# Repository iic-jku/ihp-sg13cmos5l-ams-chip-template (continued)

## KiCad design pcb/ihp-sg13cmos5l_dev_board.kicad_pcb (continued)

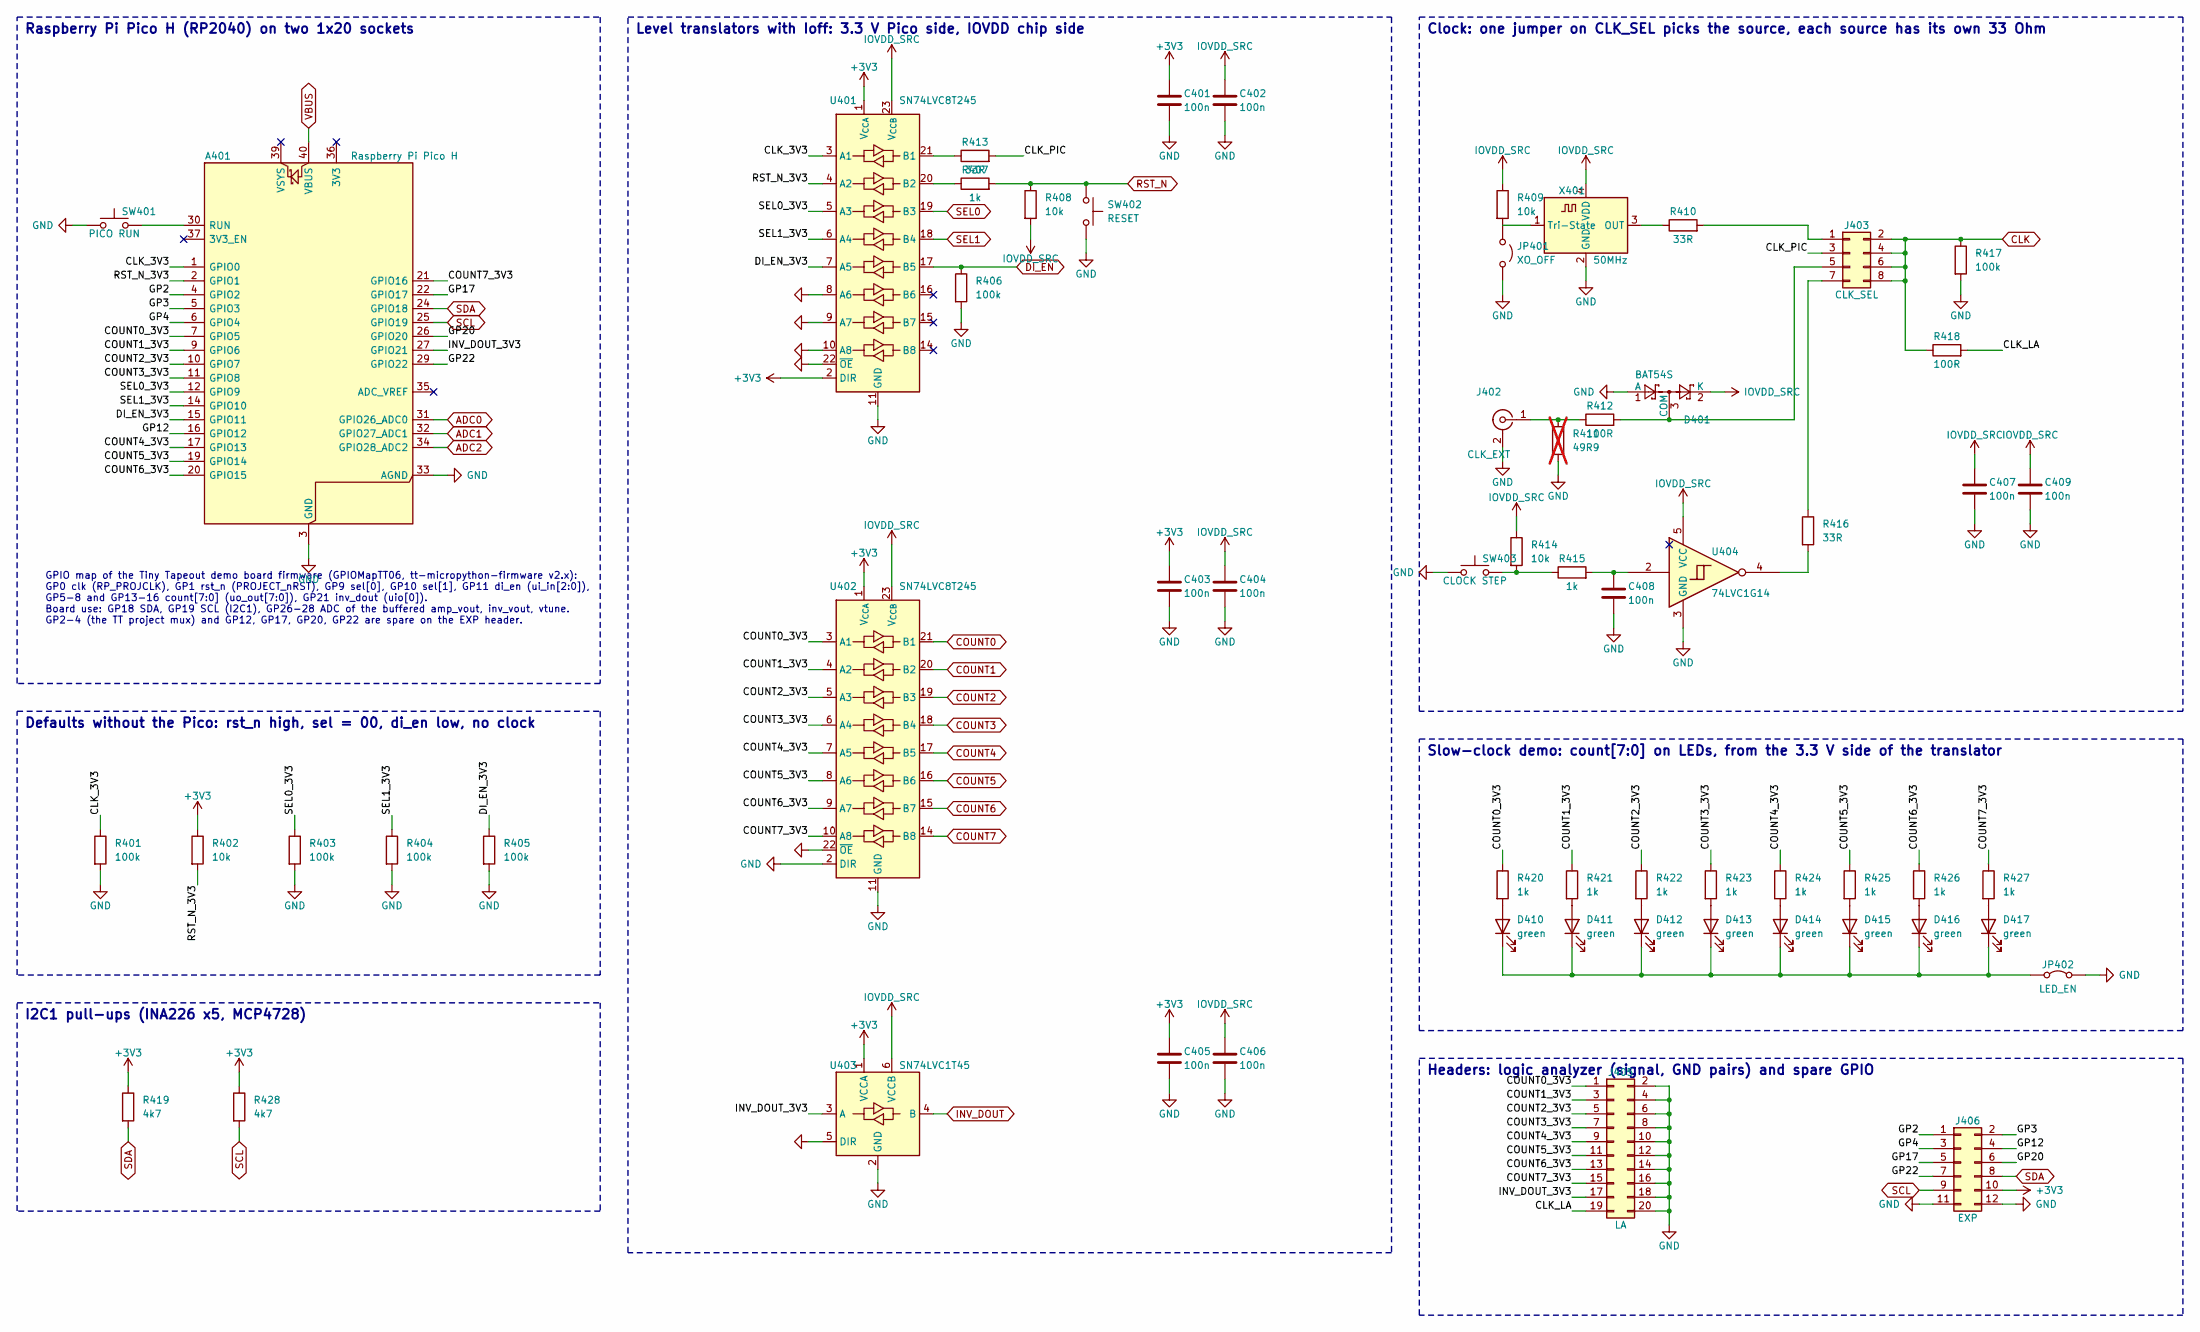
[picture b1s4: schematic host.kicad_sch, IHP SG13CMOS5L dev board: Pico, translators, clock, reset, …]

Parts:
A401: Raspberry Pi Pico H; RaspberryPi_Pico_H_Sockets; MPN SC0917
C401, C402, C403, C404, C405, C406, C407, C408, C409: 100n; C_0603_1608Metric_Pad1.08x0.95mm_HandSolder; MPN CL10B104KB8NNNC
D401: BAT54S; SOT-23; MPN BAT54SLT1G
D410, D411, D412, D413, D414, D415, D416, D417: green; LED_0603_1608Metric_Pad1.05x0.95mm_HandSolder; MPN APT1608LZGCK
J402: CLK_EXT; BNC_Amphenol_B6252HB-NPP3G-50_Horizontal_BoardEdge; MPN B6252HB-NPP3G-50
J403: CLK_SEL; PinHeader_2x04_P2.54mm_Vertical
J405: LA; PinHeader_2x10_P2.54mm_Vertical
J406: EXP; PinHeader_2x06_P2.54mm_Vertical
JP401: XO_OFF; PinHeader_1x02_P2.54mm_Vertical
JP402: LED_EN; PinHeader_1x02_P2.54mm_Vertical
R401, R403, R404, R405, R406, R417: 100k; R_0603_1608Metric_Pad0.98x0.95mm_HandSolder; MPN RC0603FR-07100KL
R402, R408, R409, R414: 10k; R_0603_1608Metric_Pad0.98x0.95mm_HandSolder; MPN RC0603FR-0710KL
R407, R415, R420, R421, R422, R423, R424, R425, R426, R427: 1k; R_0603_1608Metric_Pad0.98x0.95mm_HandSolder; MPN RC0603FR-071KL
R410, R413, R416: 33R; R_0603_1608Metric_Pad0.98x0.95mm_HandSolder; MPN RC0603FR-0733RL
R411: 49R9; R_1206_3216Metric_Pad1.30x1.75mm_HandSolder; MPN RC1206FR-0749R9L; not fitted
R412, R418: 100R; R_0603_1608Metric_Pad0.98x0.95mm_HandSolder; MPN RC0603FR-07100RL
R419, R428: 4k7; R_0603_1608Metric_Pad0.98x0.95mm_HandSolder; MPN RC0603FR-074K7L
SW401: PICO RUN; SW_TH_Tactile_Omron_B3F-100x; MPN B3F-1000
SW402: RESET; SW_TH_Tactile_Omron_B3F-100x; MPN B3F-1000
SW403: CLOCK STEP; SW_TH_Tactile_Omron_B3F-100x; MPN B3F-1000
U401, U402: SN74LVC8T245; TSSOP-24_4.4x7.8mm_P0.65mm; MPN SN74LVC8T245PWR
U403: SN74LVC1T45; SOT-23-6; MPN SN74LVC1T45DBVR
U404: 74LVC1G14; SOT-23-5; MPN SN74LVC1G14DBVR
X401: 50MHz; Oscillator_SMD_Abracon_ASE-4Pin_3.2x2.5mm_HandSoldering; MPN ECS-3225MV-500-BN-TR

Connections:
+3V3: C401.1, C403.1, C405.1, J406.10, R402.1, R419.1, R428.1, U401.1 (V_{CCA}), U401.2 (DIR), U402.1 (V_{CCA}), U403.1 (VCCA); also elsewhere on the board
/Host/CLK_3V3: A401.1 (GPIO0), R401.1, U401.3 (A1)
/Host/CLK_LA: J405.19, R418.2
/Host/CLK_PIC: J403.3, R413.2
/Host/COUNT0_3V3: A401.7 (GPIO5), J405.1, R420.1, U402.3 (A1)
/Host/COUNT1_3V3: A401.9 (GPIO6), J405.3, R421.1, U402.4 (A2)
/Host/COUNT2_3V3: A401.10 (GPIO7), J405.5, R422.1, U402.5 (A3)
/Host/COUNT3_3V3: A401.11 (GPIO8), J405.7, R423.1, U402.6 (A4)
/Host/COUNT4_3V3: A401.17 (GPIO13), J405.9, R424.1, U402.7 (A5)
/Host/COUNT5_3V3: A401.19 (GPIO14), J405.11, R425.1, U402.8 (A6)
/Host/COUNT6_3V3: A401.20 (GPIO15), J405.13, R426.1, U402.9 (A7)
/Host/COUNT7_3V3: A401.21 (GPIO16), J405.15, R427.1, U402.10 (A8)
/Host/DI_EN_3V3: A401.15 (GPIO11), R405.1, U401.7 (A5)
/Host/GP2: A401.4 (GPIO2), J406.1
/Host/GP3: A401.5 (GPIO3), J406.2
/Host/GP4: A401.6 (GPIO4), J406.3
/Host/GP12: A401.16 (GPIO12), J406.4
/Host/GP17: A401.22 (GPIO17), J406.5
/Host/GP20: A401.26 (GPIO20), J406.6
/Host/GP22: A401.29 (GPIO22), J406.7
/Host/INV_DOUT_3V3: A401.27 (GPIO21), J405.17, U403.3 (A)
/Host/RST_N_3V3: A401.2 (GPIO1), R402.2, U401.4 (A2)
/Host/SEL0_3V3: A401.12 (GPIO9), R403.1, U401.5 (A3)
/Host/SEL1_3V3: A401.14 (GPIO10), R404.1, U401.6 (A4)
ADC0: A401.31 (GPIO26_ADC0); also elsewhere on the board
ADC1: A401.32 (GPIO27_ADC1); also elsewhere on the board
ADC2: A401.34 (GPIO28_ADC2); also elsewhere on the board
CLK: J403.2, J403.4, J403.6, J403.8, R417.1, R418.1; also elsewhere on the board
COUNT0: U402.21 (B1); also elsewhere on the board
COUNT1: U402.20 (B2); also elsewhere on the board
COUNT2: U402.19 (B3); also elsewhere on the board
COUNT3: U402.18 (B4); also elsewhere on the board
COUNT4: U402.17 (B5); also elsewhere on the board
COUNT5: U402.16 (B6); also elsewhere on the board
COUNT6: U402.15 (B7); also elsewhere on the board
COUNT7: U402.14 (B8); also elsewhere on the board
DI_EN: R406.1, U401.17 (B5); also elsewhere on the board
GND: A401.3 (GND), A401.8 (GND), A401.13 (GND), A401.18 (GND), A401.23 (GND), A401.28 (GND), A401.33 (AGND), A401.38 (GND), C401.2, C402.2, C403.2, C404.2, C405.2, C406.2, C407.2, C408.2, C409.2, D401.1 (A), J402.2 (Ext), J405.2, J405.4, J405.6, J405.8, J405.10, J405.12, J405.14, J405.16, J405.18, J405.20, J406.11, J406.12, JP401.2 (B), JP402.2 (B), R401.2, R403.2, R404.2, R405.2, R406.2, R411.2, R417.2, SW401.1, SW402.2, SW403.1, U401.8 (A6), U401.9 (A7), U401.10 (A8), U401.11 (GND), U401.12 (GND), U401.13 (GND), U401.22 (~OE), U402.2 (DIR), U402.11 (GND), U402.12 (GND), U402.13 (GND), U402.22 (~OE), U403.2 (GND), U403.5 (DIR), U404.3 (GND), X401.2 (GND); also elsewhere on the board
INV_DOUT: U403.4 (B); also elsewhere on the board
IOVDD_SRC: C402.1, C404.1, C406.1, C407.1, C409.1, D401.2 (K), R408.2, R409.1, R414.1, U401.23 (V_{CCB}), U401.24 (V_{CCB}), U402.23 (V_{CCB}), U402.24 (V_{CCB}), U403.6 (VCCB), U404.5 (VCC), X401.4 (VDD); also elsewhere on the board
unnamed: A401.30 (RUN), SW401.2
unnamed: C408.1, R415.2, U404.2
unnamed: D401.3 (COM), J403.5, R412.2
unnamed: D410.2 (A), R420.2
unnamed: D410.1 (K), D411.1 (K), D412.1 (K), D413.1 (K), D414.1 (K), D415.1 (K), D416.1 (K), D417.1 (K), JP402.1 (A)
unnamed: D411.2 (A), R421.2
unnamed: D412.2 (A), R422.2
unnamed: D413.2 (A), R423.2
unnamed: D414.2 (A), R424.2
unnamed: D415.2 (A), R425.2
unnamed: D416.2 (A), R426.2
unnamed: D417.2 (A), R427.2
unnamed: J402.1 (In), R411.1, R412.1
unnamed: J403.1, R410.2
unnamed: J403.7, R416.1
unnamed: JP401.1 (A), R409.2, X401.1 (Tri-State)
unnamed: R414.2, R415.1, SW403.2
unnamed: R416.2, U404.4
unnamed: R413.1, U401.21 (B1)
unnamed: R407.1, U401.20 (B2)
unnamed: R410.1, X401.3 (OUT)
RST_N: R407.2, R408.1, SW402.1; also elsewhere on the board
SCL: A401.25 (GPIO19), J406.9, R428.2; also elsewhere on the board
SDA: A401.24 (GPIO18), J406.8, R419.2; also elsewhere on the board
SEL0: U401.19 (B3); also elsewhere on the board
SEL1: U401.18 (B4); also elsewhere on the board
VBUS: A401.40 (VBUS); also elsewhere on the board

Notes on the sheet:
Raspberry Pi Pico H (RP2040) on two 1x20 sockets
GPIO map of the Tiny Tapeout demo board firmware (GPIOMapTT06, tt-micropython-firmware v2.x): GP0 clk (RP_PROJCLK), GP1 rst_n (PROJECT_nRST), GP9 sel[0], GP10 sel[1], GP11 di_en (ui_in[2:0]), GP5-8 and GP13-16 count[7:0] (uo_out[7:0]), GP21 inv_dout (uio[0]). Board use: GP18 SDA, GP19 SCL (I2C1), G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
Defaults without the Pico: rst_n high, sel = 00, di_en low, no clock
I2C1 pull-ups (INA226 x5, MCP4728)
Level translators with Ioff: 3.3 V Pico side, IOVDD chip side
Clock: one jumper on CLK_SEL picks the source, each source has its own 33 Ohm
Slow-clock demo: count[7:0] on LEDs, from the 3.3 V side of the translator
Headers: logic analyzer (signal, GND pairs) and spare GPIO

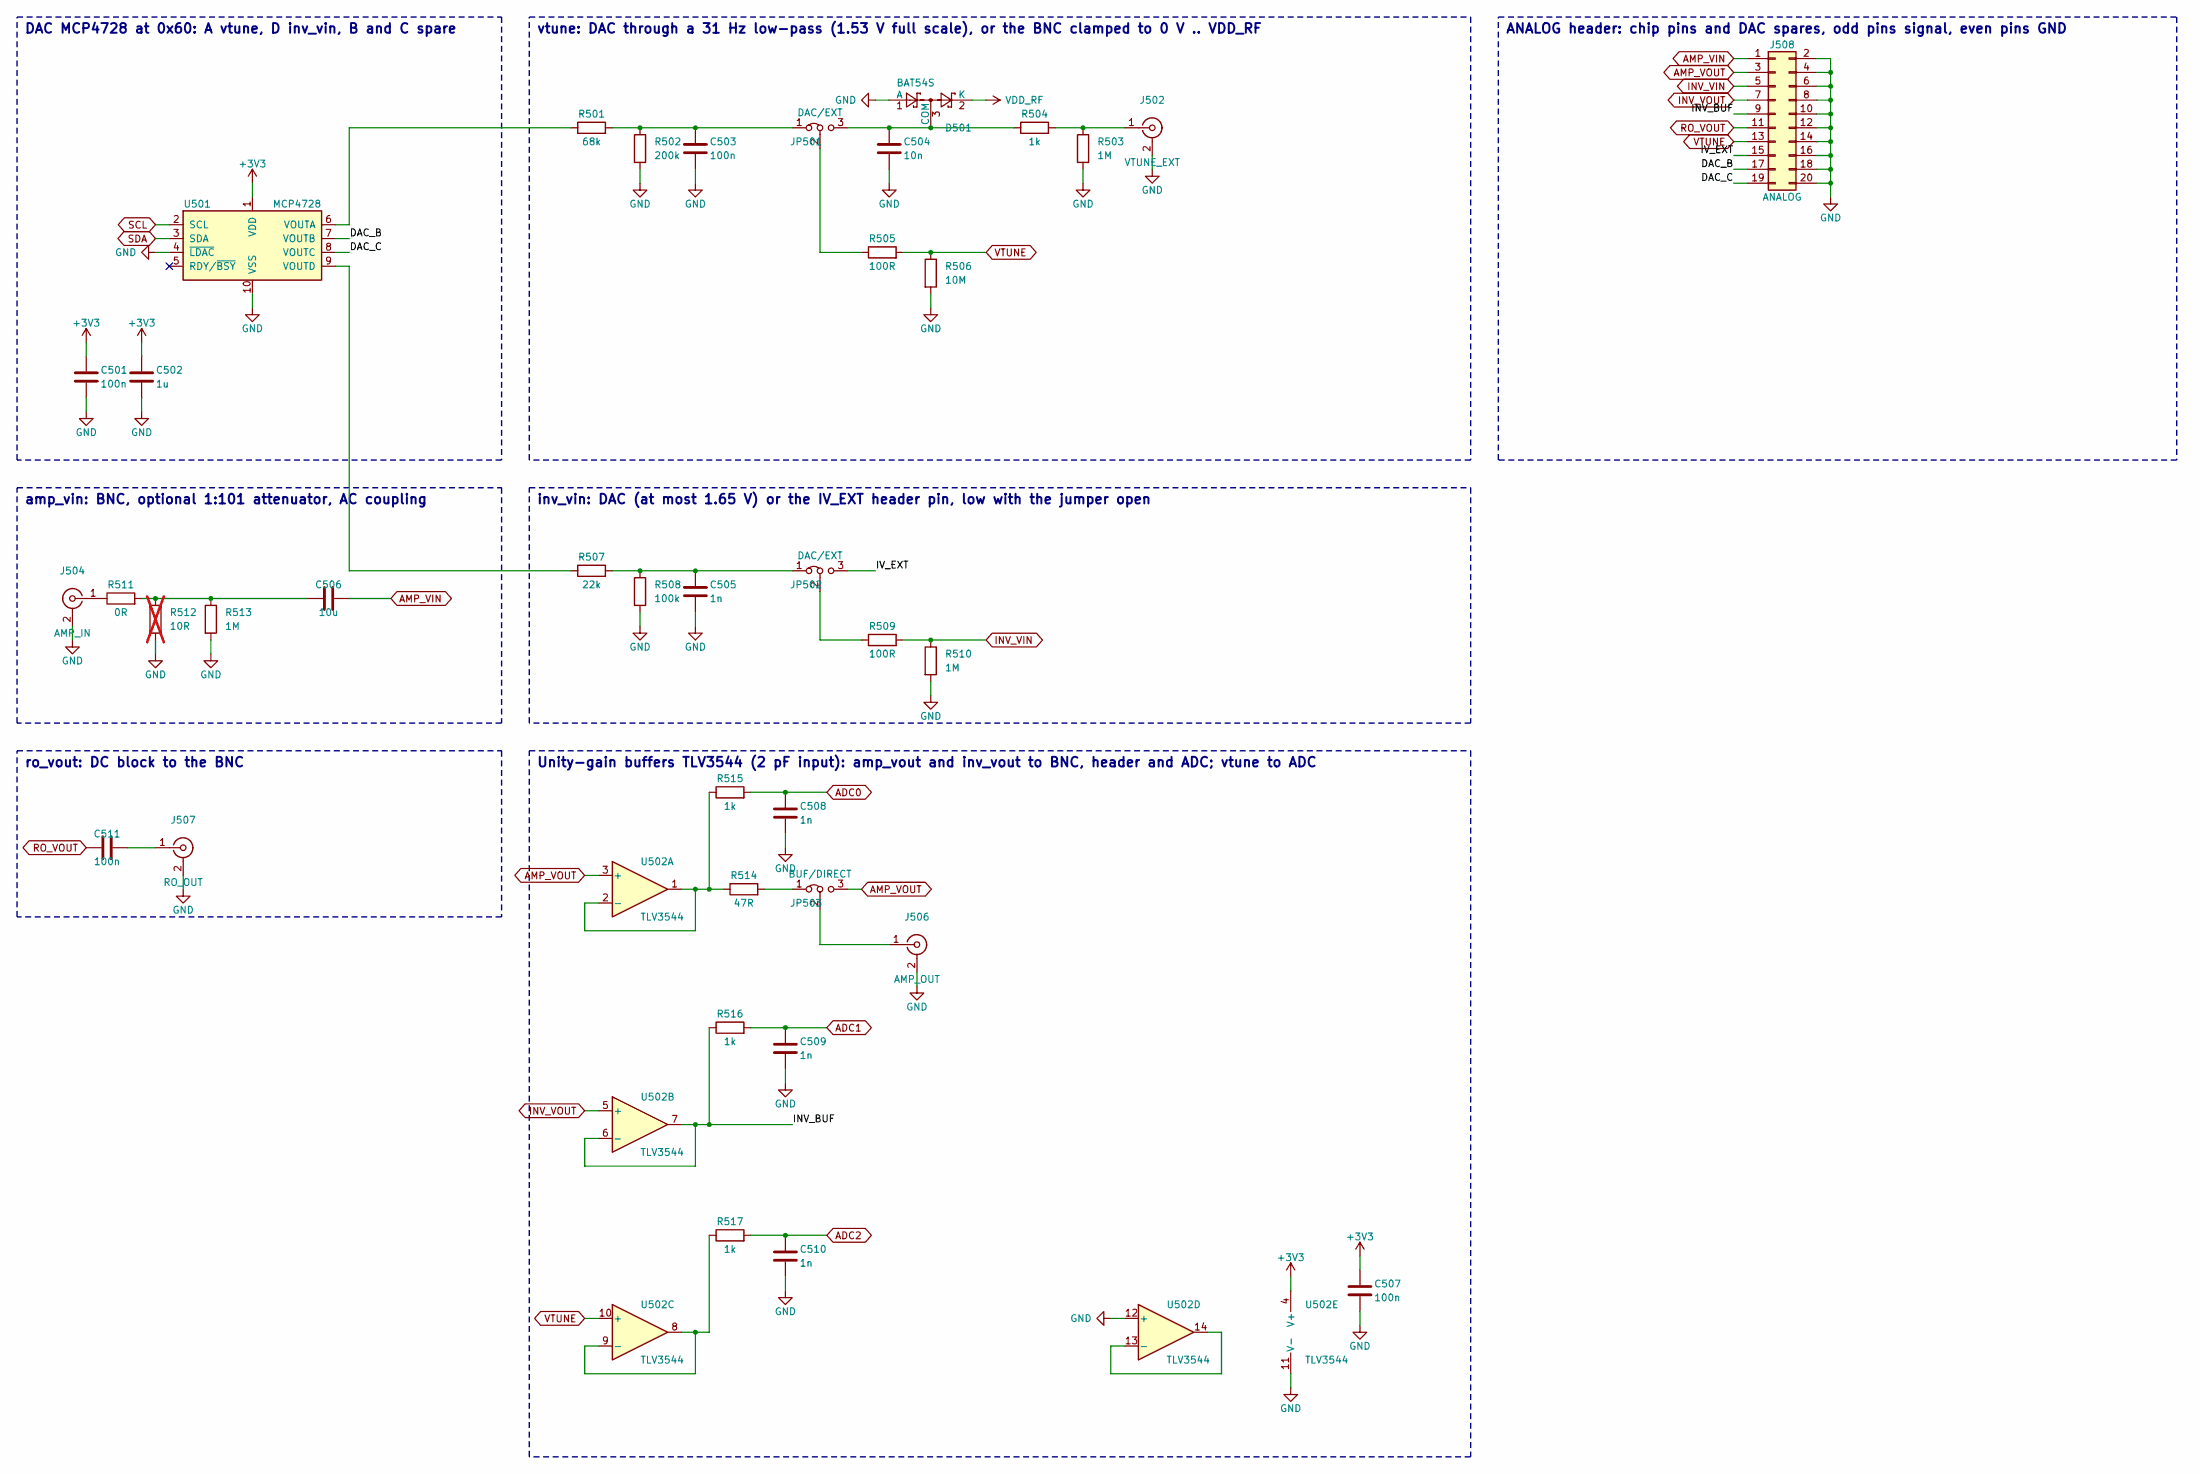
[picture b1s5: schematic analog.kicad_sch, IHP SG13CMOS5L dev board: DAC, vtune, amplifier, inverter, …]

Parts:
C501, C507, C511: 100n; C_0603_1608Metric_Pad1.08x0.95mm_HandSolder; MPN CL10B104KB8NNNC
C502: 1u; C_0603_1608Metric_Pad1.08x0.95mm_HandSolder; MPN CL10B105KO8NNNC
C503: 100n; C_1206_3216Metric_Pad1.33x1.80mm_HandSolder; MPN GRM31C5C1H104JA01L
C504: 10n; C_0603_1608Metric_Pad1.08x0.95mm_HandSolder; MPN GRM1885C1H103JA01D
C505, C508, C509, C510: 1n; C_0603_1608Metric_Pad1.08x0.95mm_HandSolder; MPN CL10C102JB8NNNC
C506: 10u; C_1206_3216Metric_Pad1.33x1.80mm_HandSolder; MPN GRM31CR71E106KA12L
D501: BAT54S; SOT-23; MPN BAT54SLT1G
J502: VTUNE_EXT; BNC_Amphenol_B6252HB-NPP3G-50_Horizontal_BoardEdge; MPN B6252HB-NPP3G-50
J504: AMP_IN; BNC_Amphenol_B6252HB-NPP3G-50_Horizontal_BoardEdge; MPN B6252HB-NPP3G-50
J506: AMP_OUT; BNC_Amphenol_B6252HB-NPP3G-50_Horizontal_BoardEdge; MPN B6252HB-NPP3G-50
J507: RO_OUT; BNC_Amphenol_B6252HB-NPP3G-50_Horizontal_BoardEdge; MPN B6252HB-NPP3G-50
J508: ANALOG; PinHeader_2x10_P2.54mm_Vertical
JP501, JP502: DAC/EXT; PinHeader_1x03_P2.54mm_Vertical
JP503: BUF/DIRECT; PinHeader_1x03_P2.54mm_Vertical
R501: 68k; R_0603_1608Metric_Pad0.98x0.95mm_HandSolder; MPN RC0603FR-0768KL
R502: 200k; R_0603_1608Metric_Pad0.98x0.95mm_HandSolder; MPN RC0603FR-07200KL
R503, R510, R513: 1M; R_0603_1608Metric_Pad0.98x0.95mm_HandSolder; MPN RC0603FR-071ML
R504, R515, R516, R517: 1k; R_0603_1608Metric_Pad0.98x0.95mm_HandSolder; MPN RC0603FR-071KL
R505, R509: 100R; R_0603_1608Metric_Pad0.98x0.95mm_HandSolder; MPN RC0603FR-07100RL
R506: 10M; R_0603_1608Metric_Pad0.98x0.95mm_HandSolder; MPN RC0603FR-0710ML
R507: 22k; R_0603_1608Metric_Pad0.98x0.95mm_HandSolder; MPN RC0603FR-0722KL
R508: 100k; R_0603_1608Metric_Pad0.98x0.95mm_HandSolder; MPN RC0603FR-07100KL
R511: 0R; R_0603_1608Metric_Pad0.98x0.95mm_HandSolder; MPN RC0603JR-070RL
R512: 10R; R_0603_1608Metric_Pad0.98x0.95mm_HandSolder; MPN RC0603FR-0710RL; not fitted
R514: 47R; R_0603_1608Metric_Pad0.98x0.95mm_HandSolder; MPN RC0603FR-0747RL
U501: MCP4728; MSOP-10_3x3mm_P0.5mm; MPN MCP4728-E/UN
U502: TLV3544; TSSOP-14_4.4x5mm_P0.65mm; MPN TLV3544IPWR

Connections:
+3V3: C501.1, C502.1, C507.1, U501.1 (VDD), U502.4 (V+); also elsewhere on the board
/Analog/DAC_B: J508.17, U501.7 (VOUTB)
/Analog/DAC_C: J508.19, U501.8 (VOUTC)
/Analog/INV_BUF: J508.9, R516.1, U502.6 (-), U502.7
/Analog/IV_EXT: J508.15, JP502.3 (B)
ADC0: C508.1, R515.2; also elsewhere on the board
ADC1: C509.1, R516.2; also elsewhere on the board
ADC2: C510.1, R517.2; also elsewhere on the board
AMP_VIN: C506.2, J508.1; also elsewhere on the board
AMP_VOUT: J508.3, JP503.3 (B), U502.3 (+); also elsewhere on the board
GND: C501.2, C502.2, C503.2, C504.2, C505.2, C507.2, C508.2, C509.2, C510.2, D501.1 (A), J502.2 (Ext), J504.2 (Ext), J506.2 (Ext), J507.2 (Ext), J508.2, J508.4, J508.6, J508.8, J508.10, J508.12, J508.14, J508.16, J508.18, J508.20, R502.2, R503.2, R506.2, R508.2, R510.2, R512.2, R513.2, U501.4 (~LDAC), U501.10 (VSS), U502.11 (V-), U502.12 (+); also elsewhere on the board
INV_VIN: J508.5, R509.2, R510.1; also elsewhere on the board
INV_VOUT: J508.7, U502.5 (+); also elsewhere on the board
unnamed: C506.1, R511.2, R512.1, R513.1
unnamed: C504.1, D501.3 (COM), JP501.3 (B), R504.1
unnamed: J502.1 (In), R503.1, R504.2
unnamed: J504.1 (In), R511.1
unnamed: J506.1 (In), JP503.2 (C)
unnamed: C511.2, J507.1 (In)
unnamed: C503.1, JP501.1 (A), R501.2, R502.1
unnamed: JP501.2 (C), R505.1
unnamed: C505.1, JP502.1 (A), R507.2, R508.1
unnamed: JP502.2 (C), R509.1
unnamed: JP503.1 (A), R514.2
unnamed: R501.1, U501.6 (VOUTA)
unnamed: R507.1, U501.9 (VOUTD)
unnamed: R514.1, R515.1, U502.1, U502.2 (-)
unnamed: R517.1, U502.8, U502.9 (-)
unnamed: U502.13 (-), U502.14
RO_VOUT: C511.1, J508.11; also elsewhere on the board
SCL: U501.2 (SCL); also elsewhere on the board
SDA: U501.3 (SDA); also elsewhere on the board
VDD_RF: D501.2 (K); also elsewhere on the board
VTUNE: J508.13, R505.2, R506.1, U502.10 (+); also elsewhere on the board

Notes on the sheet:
DAC MCP4728 at 0x60: A vtune, D inv_vin, B and C spare
vtune: DAC through a 31 Hz low-pass (1.53 V full scale), or the BNC clamped to 0 V .. VDD_RF
inv_vin: DAC (at most 1.65 V) or the IV_EXT header pin, low with the jumper open
amp_vin: BNC, optional 1:101 attenuator, AC coupling
ro_vout: DC block to the BNC
Unity-gain buffers TLV3544 (2 pF input): amp_vout and inv_vout to BNC, header and ADC; vtune to ADC
ANALOG header: chip pins and DAC spares, odd pins signal, even pins GND

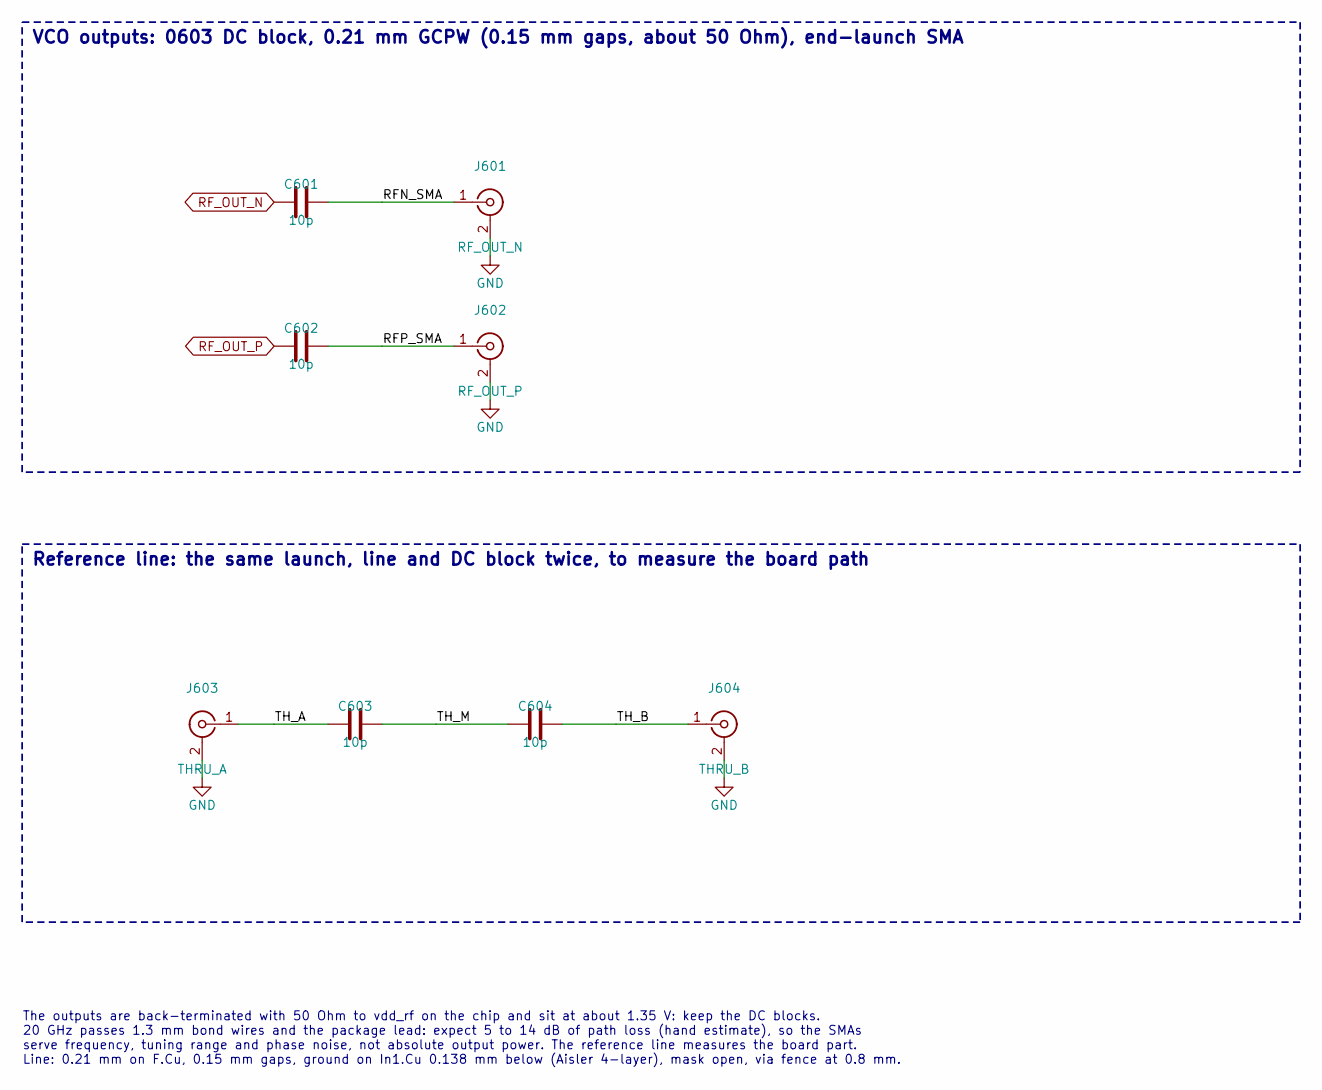
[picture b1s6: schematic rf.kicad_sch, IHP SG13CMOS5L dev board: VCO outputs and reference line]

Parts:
C601, C602, C603, C604: 10p; C_0603_1608Metric; MPN GRM1885C1H100JA01D
J601: RF_OUT_N; SMA_Cinch_142-0761-881_EndLaunch; MPN 142-0761-881
J602: RF_OUT_P; SMA_Cinch_142-0761-881_EndLaunch; MPN 142-0761-881
J603: THRU_A; SMA_Cinch_142-0761-881_EndLaunch; MPN 142-0761-881
J604: THRU_B; SMA_Cinch_142-0761-881_EndLaunch; MPN 142-0761-881

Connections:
/RF/RFN_SMA: C601.2, J601.1 (In)
/RF/RFP_SMA: C602.2, J602.1 (In)
/RF/TH_A: C603.1, J603.1 (In)
/RF/TH_B: C604.2, J604.1 (In)
/RF/TH_M: C603.2, C604.1
GND: J601.2 (Ext), J602.2 (Ext), J603.2 (Ext), J604.2 (Ext); also elsewhere on the board
RF_OUT_N: C601.1; also elsewhere on the board
RF_OUT_P: C602.1; also elsewhere on the board

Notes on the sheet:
VCO outputs: 0603 DC block, 0.21 mm GCPW (0.15 mm gaps, about 50 Ohm), end-launch SMA
Reference line: the same launch, line and DC block twice, to measure the board path
The outputs are back-terminated with 50 Ohm to vdd_rf on the chip and sit at about 1.35 V: keep the DC blocks. 20 GHz passes 1.3 mm bond wires and the package lead: expect 5 to 14 dB of path loss (hand estimate), so the SMAs serve frequency, tuning range and phase noise, not absolute output power. 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

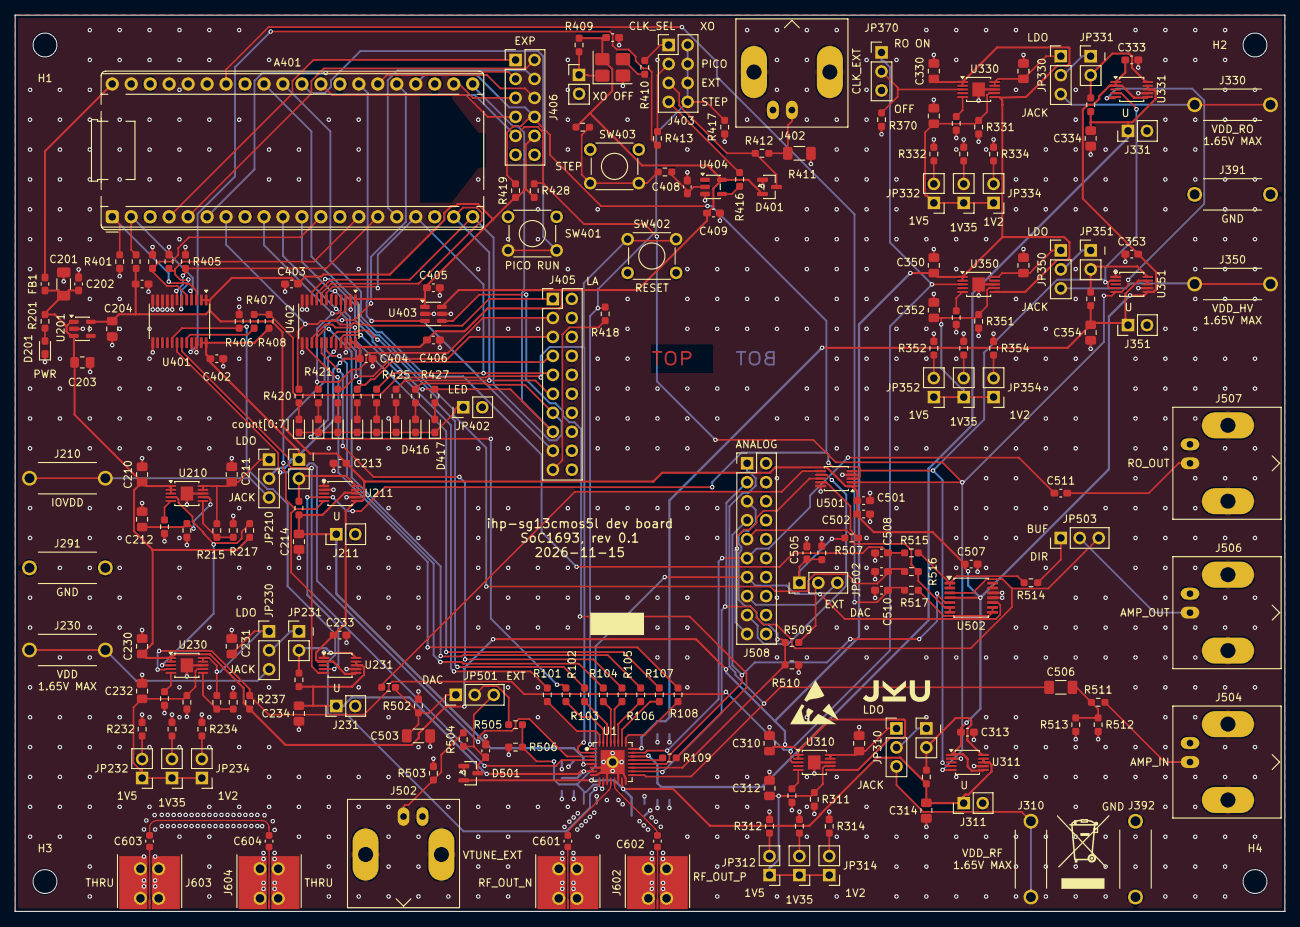
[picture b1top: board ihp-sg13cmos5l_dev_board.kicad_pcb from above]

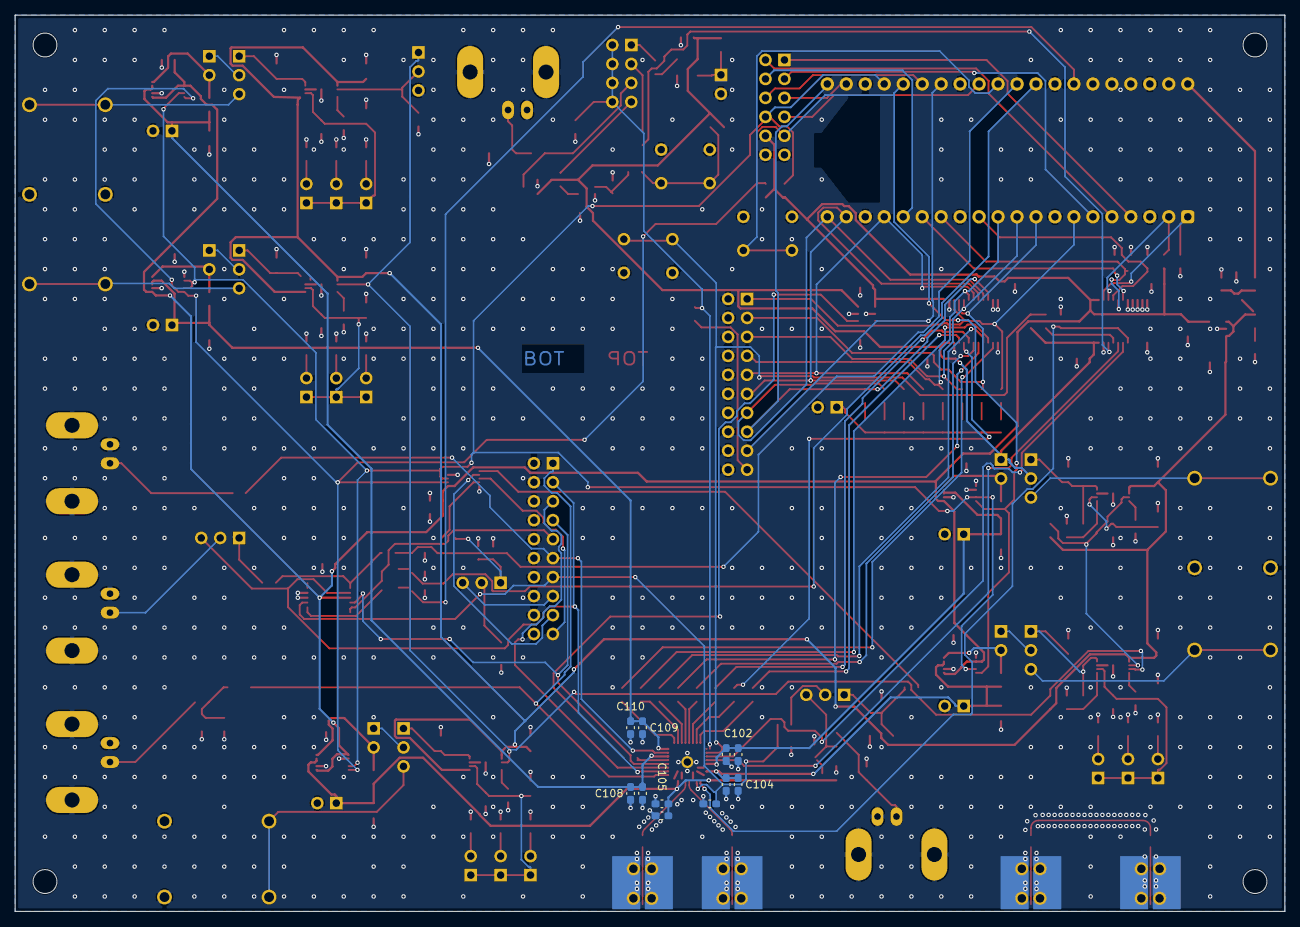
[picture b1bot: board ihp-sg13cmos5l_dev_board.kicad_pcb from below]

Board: 4 copper layers, 170.0 x 120.0 mm, 249 parts (11 on the bottom side), 162 nets.

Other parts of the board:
LOGO1: Logo_JKU_9.0x2.9mm
LOGO2: Logo_ESD_6.5x5.9mm
LOGO3: Logo_WEEE_7.0x9.9mm

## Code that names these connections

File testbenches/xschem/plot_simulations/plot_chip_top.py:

# -*- coding: utf-8 -*-
# SPDX-FileCopyrightText: 2026 Simon Dorrer and Harald Pretl
# SPDX-License-Identifier: Apache-2.0 WITH SHL-2.1
# Author: Simon Dorrer
# Description: Transient plots for the chip top-level testbench based on ngspice exports.
# Created: 12.05.2026
# Last Modified: 08.11.2026
# ============================================

# Imports
import numpy as np
import matplotlib.pyplot as plt
import ngspice2python as ng
from pathlib import Path
# ============================================

# Plotting Configuration
# ============================================
# Interactive mode stays off: the plt.show() at the end of main() then blocks in the GUI
# event loop, which is what draws the windows in the first place. With plt.ion() the call
# returns immediately and nothing pumps that loop afterwards, so no window ever appears.
plt.close("all")

# Matplotlib Settings
# %matplotlib qt
# %matplotlib inline

# Pure Matplotlib text rendering (no external LaTeX dependency)
plt.rcParams.update({
    "text.usetex": False,
    "mathtext.fontset": "cm",
    "font.family": "serif",
    "font.size": 12,
})
# =========================================================================

def plot_digital(fig_title, signals, data_time, figures_dir, filename, fig_height=9):
    """Stack digital signals in separate subplots sharing the time axis."""
    y_ticks = [0.0, 1.0, 2.0, 3.0, 4.0]
    fig, axs = plt.subplots(len(signals), sharex=True)
    if len(signals) == 1:
        axs = [axs]
    fig.set_figwidth(16)
    fig.set_figheight(fig_height)
    fig.suptitle(fig_title)

    for ax, (name, values, color) in zip(axs, signals):
        ax.plot(data_time, values, color=color, linewidth=1.3)
        ax.set_ylabel(f'{name} (V)', fontsize=11)
        ax.set_ylim(-0.2, 4.2)
        ax.set_yticks(y_ticks)
        ax.set_yticklabels(["0", "1.0", "2.0", "3.0", "4.0"], fontsize=8)
        ax.tick_params(axis='x', labelsize=8)
        ax.grid(True, alpha=0.4)

    axs[-1].set_xlabel(r'$t$ ($\mu$s)')
    fig.tight_layout(rect=[0, 0, 1, 0.98], pad=0.5, w_pad=0.1, h_pad=0.1)
    fig.savefig(str(figures_dir / f"{filename}.svg"), bbox_inches='tight')
    fig.savefig(str(figures_dir / f"{filename}.pdf"), bbox_inches='tight')
    return fig
# =========================================================================

def moving_average(time_us, values, window_us):
    """Average over window_us after resampling on a uniform grid, ngspice writes a non-uniform time axis."""
    grid = np.arange(time_us[0], time_us[-1], window_us / 200.0)
    uniform = np.interp(grid, time_us, values)
    return grid, np.convolve(uniform, np.ones(200) / 200.0, mode="same")
# =========================================================================

def main():
    # Resolve data and output paths relative to this script
    script_dir = Path(__file__).resolve().parent
    data_dir = script_dir / "data"
    figures_dir = script_dir / "figures"
    figures_dir.mkdir(parents=True, exist_ok=True)

    # ------------------------------------------------------------------
    # 1. Load ngspice transient simulation data
    # ------------------------------------------------------------------
    ngspice_file = str(data_dir / "chip_top_tb_tran.txt")

    time     = ng.loadngspicecol(ngspice_file, "time")
    rst_n    = ng.loadngspicecol(ngspice_file, "v(rst_n)")
    sel1     = ng.loadngspicecol(ngspice_file, "v(sel1)")
    sel0     = ng.loadngspicecol(ngspice_file, "v(sel0)")
    count    = [ng.loadngspicecol(ngspice_file, f"v(count{i})") for i in range(8)]
    inv_dout = ng.loadngspicecol(ngspice_file, "v(inv_dout)")
    inv_vin  = ng.loadngspicecol(ngspice_file, "v(inv_vin)")
    inv_vout = ng.loadngspicecol(ngspice_file, "v(inv_vout)")
    amp_vin  = ng.loadngspicecol(ngspice_file, "v(amp_vin)")
    amp_vout = ng.loadngspicecol(ngspice_file, "v(amp_vout)")
    ro_vout  = ng.loadngspicecol(ngspice_file, "v(ro_vout)")
    i_vdd    = ng.loadngspicecol(ngspice_file, "i(vvdd)")
    i_hv     = ng.loadngspicecol(ngspice_file, "i(vhv)")

    # Display-friendly axis scale
    time_us = time * 1e6

    # ------------------------------------------------------------------
    # 2. Plot 1 (digital): reset, counter select and the chip outputs
    # ------------------------------------------------------------------
    colors = ["#ff6b35", "#845ec2", "#2c73d2", "#008f7a", "#c34a36", "#4d8076", "#7b2cbf", "#b39f00"]
    signals = [
        ("RST_n", rst_n, "#00b945"),
        ("SEL1",  sel1,  "#0c5da5"),
        ("SEL0",  sel0,  "#ff9500"),
    ]
    signals += [(f"COUNT{i}", count[i], colors[i]) for i in range(8)]
    signals += [("INV_DOUT", inv_dout, "#e63946")]
    plot_digital(
        "Chip Top: Counter Select and Digital Outputs",
        signals, time_us, figures_dir,
        "chip_top_tb_tran_digital",
        fig_height=13,
    )

    # ------------------------------------------------------------------
    # 3. Plot 2 (analog): inverter, amplifier and ring oscillator
    # ------------------------------------------------------------------
    fig2, (ax1, ax2, ax3) = plt.subplots(3)
    fig2.set_figwidth(14)
    fig2.set_figheight(10)
    fig2.suptitle("Chip Top: Analog Macros")

    ax1.plot(time_us, inv_vin,  color="#0c5da5", linewidth=1.5, label=r'$V_\mathrm{in}$')
    ax1.plot(time_us, inv_vout, color="#ff6b35", linewidth=1.5, label=r'$V_\mathrm{out}$')
    ax1.set_ylabel(r'$V$ (V)')
    ax1.set_xlabel(r'$t$ ($\mu$s)')
    ax1.set_title("Inverter, Analog Channel (200 kHz)")
    ax1.legend(loc='best', fontsize=10)
    ax1.grid(True, alpha=0.4)

    ax2.plot(time_us, amp_vin,  color="#2c73d2", linewidth=1.5, label=r'$V_\mathrm{in}$')
    ax2.plot(time_us, amp_vout, color="#c34a36", linewidth=1.5, label=r'$V_\mathrm{out}$')
    ax2.set_ylabel(r'$V$ (V)')
    ax2.set_xlabel(r'$t$ ($\mu$s)')
    ax2.set_title("Amplifier (1 MHz)")
    ax2.legend(loc='best', fontsize=10)
    ax2.grid(True, alpha=0.4)

    # A few periods at the end of the run, when the ring oscillator has settled
    zoom = time_us > time_us[-1] - 0.02
    ax3.plot(time_us[zoom], ro_vout[zoom], color="#008f7a", linewidth=1.5)
    ax3.set_ylabel(r'$V_\mathrm{out}$ (V)')
    ax3.set_xlabel(r'$t$ ($\mu$s)')
    ax3.set_title("Ring Oscillator")
    ax3.grid(True, alpha=0.4)

    fig2.tight_layout(rect=[0, 0, 1, 0.98])
    fig2.savefig(str(figures_dir / "chip_top_tb_tran_analog.svg"), bbox_inches='tight')
    fig2.savefig(str(figures_dir / "chip_top_tb_tran_analog.pdf"), bbox_inches='tight')

    # ------------------------------------------------------------------
    # 4. Plot 3 (supply): average current of the core and the IHP HV counter
    # ------------------------------------------------------------------
    fig3, ax = plt.subplots()
    fig3.set_figwidth(14)
    fig3.set_figheight(5)
    fig3.suptitle("Chip Top: Supply Current, Averaged over 100 ns")

    # A source sinks the supply current into its positive terminal, so the sign is flipped
    for values, color, label in ((i_vdd, "#0c5da5", "VDD (core)"), (i_hv, "#ff6b35", "vdd_hv (IHP HV counter)")):
        grid, avg = moving_average(time_us, -values, 0.1)
        ax.plot(grid, avg * 1e3, color=color, linewidth=1.5, label=label)
    ax.set_ylabel(r'$I$ (mA)')
    ax.set_xlabel(r'$t$ ($\mu$s)')
    ax.legend(loc='best', fontsize=10)
    ax.grid(True, alpha=0.4)

    fig3.tight_layout(rect=[0, 0, 1, 0.98])
    fig3.savefig(str(figures_dir / "chip_top_tb_tran_supply.svg"), bbox_inches='tight')
    fig3.savefig(str(figures_dir / "chip_top_tb_tran_supply.pdf"), bbox_inches='tight')

    # ------------------------------------------------------------------
    # 5. Open the plot windows (blocks until they are closed)
    # ------------------------------------------------------------------
    plt.show()
    # ============================================

# Main Execution
if __name__ == '__main__':
    main()
# =========================================================================
